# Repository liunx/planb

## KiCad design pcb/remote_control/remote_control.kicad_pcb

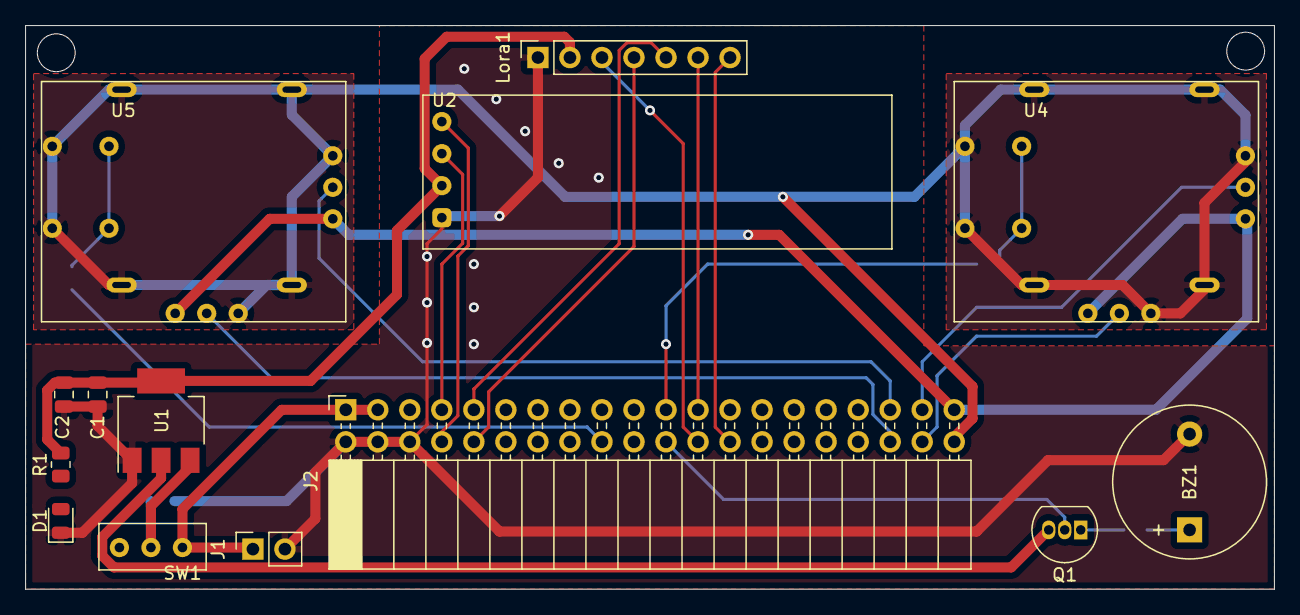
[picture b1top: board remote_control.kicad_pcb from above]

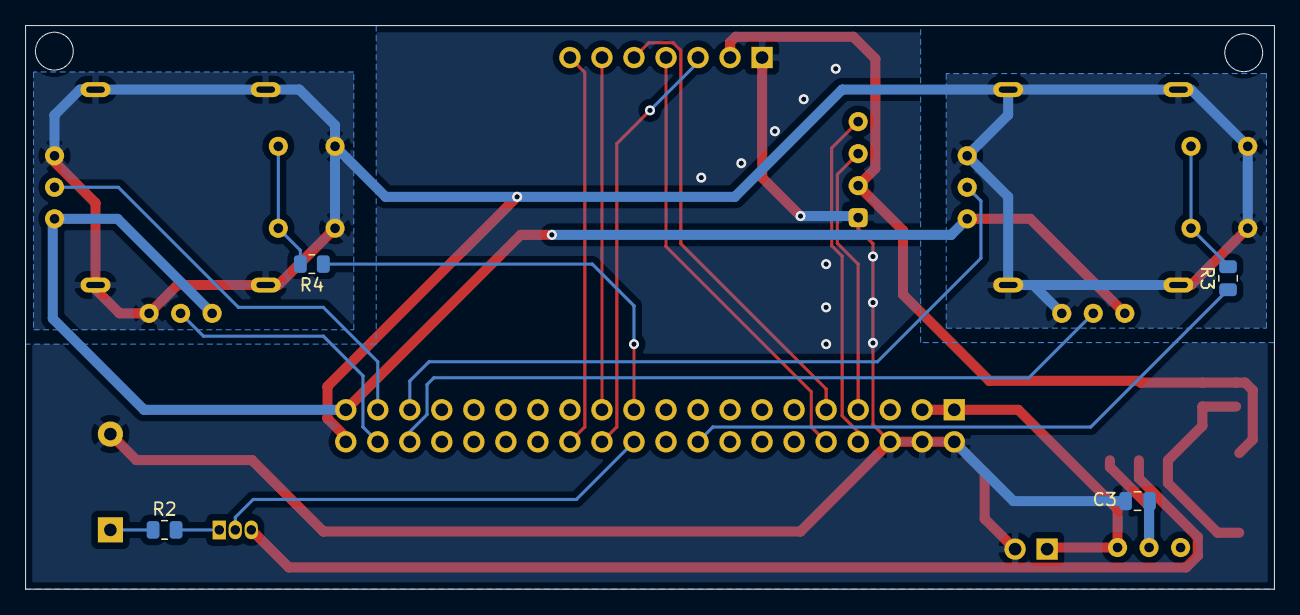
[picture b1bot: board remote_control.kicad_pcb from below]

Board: 2 copper layers, 99.1 x 44.7 mm, 18 parts (4 on the bottom side), 25 nets.

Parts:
BZ1: Buzzer; Buzzer_12x9.5RM7.6
C1, C3: 10uF; C_0805_2012Metric
C2: 100nF; C_0805_2012Metric
D1: LED; LED_0805_2012Metric
J1: Conn_01x02; PinSocket_1x02_P2.54mm_Vertical
J2: Conn_02x20_Odd_Even; PinSocket_2x20_P2.54mm_Horizontal
Lora1: Conn_01x07; PinSocket_1x07_P2.54mm_Vertical
Q1: S8050; TO-92_Inline
R1, R2, R3, R4: 510R; R_0805_2012Metric
SW1: SW_Push; SS12D00
U1: AMS1117-5.0; SOT-223-3_TabPin2
U2: OLED0.91''; OLED_0.91
U4, U5: Rocker

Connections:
+3.3VA: J2.39, U4.5, U5.5
+5V: C1.1, C2.1, Lora1.2, Q1.3, R1.2, U1.2, U2.2
/PA0: J2.37, U4.1
/PA1: J2.38, U4.2
/PA2: J2.35, U5.1
/PA3: J2.36, U5.2
/PA8: J2.22, Q1.2
/PA12: J2.18, R3.1
/PB6: J2.9, Lora1.5
/PB7: J2.10, Lora1.4
/PB8: J2.7, U2.3
/PB9: J2.8, U2.4
/PB12: J2.26, Lora1.7
/PB13: J2.23, Lora1.6
/PB14: J2.24, Lora1.3
/PB15: J2.21, R4.1
GNDA: J2.40, U4.4, U5.4
GNDD: BZ1.2, C1.2, C2.2, C3.2, D1.1, J1.2, J2.2, J2.4, J2.6, Lora1.1, U1.1, U2.1
unnamed: BZ1.1, R2.1
unnamed: C3.1, SW1.2, U1.3
unnamed: D1.2, R1.1
unnamed: Q1.1, R2.2
unnamed: R3.2, U5.3
unnamed: R4.2, U4.3
VCC: J1.1, J2.1, J2.3, SW1.1

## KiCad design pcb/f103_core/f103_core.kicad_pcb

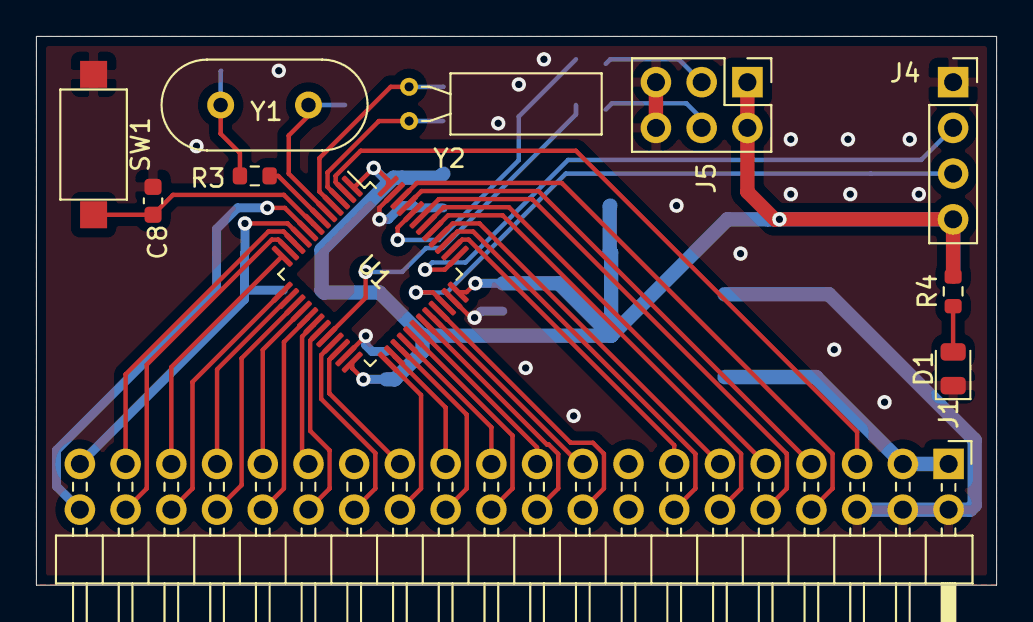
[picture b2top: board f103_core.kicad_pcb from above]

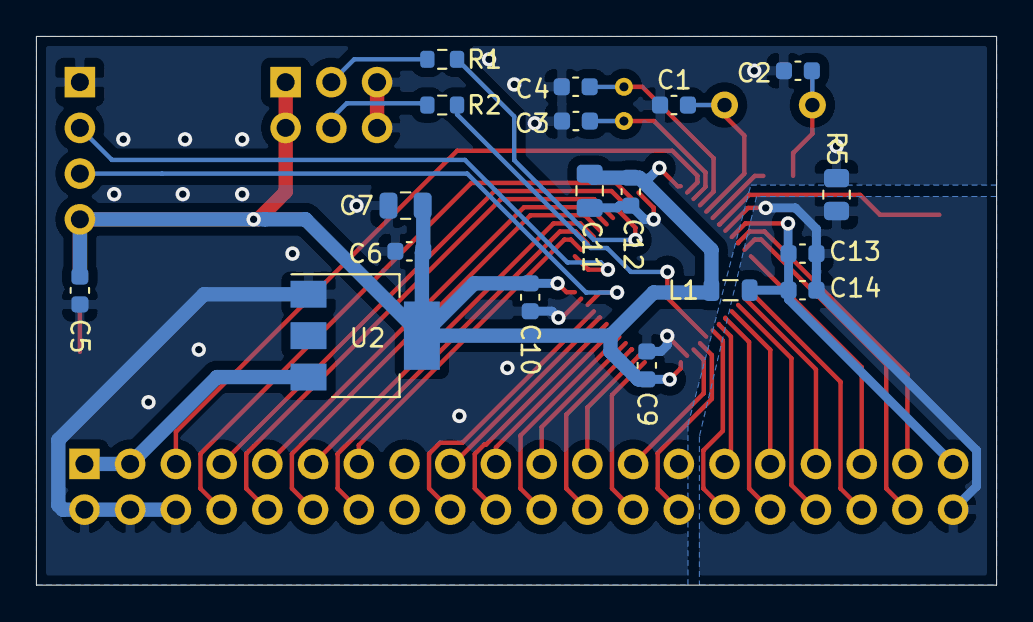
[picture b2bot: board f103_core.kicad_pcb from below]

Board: 2 copper layers, 53.3 x 30.5 mm, 29 parts (18 on the bottom side), 48 nets.

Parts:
C1, C2: 20pF; C_0603_1608Metric
C3, C4, C8: 10pF; C_0603_1608Metric
C5, C7, C9, C10, C12: 100nF; C_0603_1608Metric
C6: 10uF; C_0805_2012Metric
C11: 4.7uF; C_0805_2012Metric
C13: 1uF; C_0603_1608Metric
C14: 10nF; C_0603_1608Metric
D1: LED; LED_0805_2012Metric
J1: Conn_02x20_Odd_Even; PinHeader_2x20_P2.54mm_Horizontal
J4: Conn_01x04; PinSocket_1x04_P2.54mm_Vertical
J5: Conn_02x03_Odd_Even; PinHeader_2x03_P2.54mm_Vertical
L1: 10uH; L_0805_2012Metric
R1, R2: 10K; R_0603_1608Metric
R3: 390; R_0603_1608Metric
R4: 510R; R_0603_1608Metric
R5: 0R; R_0805_2012Metric
SW1: SW_Push; SW_SPST_CK_RS282G05A3
U1: STM32F103C6Tx; LQFP-48_7x7mm_P0.5mm
U2: AMS1117-3.3; SOT-223-3_TabPin2
Y1: 8M; Crystal_HC49-4H_Vertical
Y2: 32.768; Crystal_C38-LF_D3.0mm_L8.0mm_Horizontal

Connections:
+3.3VA: C13.1, C14.1, J1.39, L1.2, U1.9
+3V3: C5.1, C6.1, C7.1, C9.1, C10.1, C11.1, C12.1, J4.4, J5.1, J5.2, L1.1, R4.2, U1.1, U1.24, U1.36, U1.48, U2.2
/BOOT0: R1.2, U1.44
/BOOT1: R2.1, U1.20
/PA0: J1.37, U1.10
/PA1: J1.38, U1.11
/PA2: J1.35, U1.12
/PA3: J1.36, U1.13
/PA4: J1.33, U1.14
/PA5: J1.34, U1.15
/PA6: J1.31, U1.16
/PA7: J1.32, U1.17
/PA8: J1.22, U1.29
/PA9: J1.19, U1.30
/PA10: J1.20, U1.31
/PA11: J1.17, U1.32
/PA12: J1.18, U1.33
/PA15: J1.13, U1.38
/PB0: J1.29, U1.18
/PB1: J1.30, U1.19
/PB3: J1.14, U1.39
/PB4: J1.11, U1.40
/PB5: J1.12, U1.41
/PB6: J1.9, U1.42
/PB7: J1.10, U1.43
/PB8: J1.7, U1.45
/PB9: J1.8, U1.46
/PB10: J1.28, U1.21
/PB11: J1.25, U1.22
/PB12: J1.26, U1.25
/PB13: J1.23, U1.26
/PB14: J1.24, U1.27
/PB15: J1.21, U1.28
/PC13: J1.5, U1.2
/RCC_OSC32_IN: C3.2, U1.3, Y2.1
/RCC_OSC32_OUT: C4.2, U1.4, Y2.2
/RCC_OSC_IN: C1.2, U1.5, Y1.1
/RCC_OSC_OUT: R3.2, U1.6
/SYS_JTCK-SWCL: J4.2, U1.37
/SYS_JTMS-SWDIO: J4.3, U1.34
GND: C1.1, C2.1, C3.1, C4.1, C5.2, C6.2, C7.2, C8.2, C9.2, C10.2, C11.2, C12.2, D1.1, J1.2, J1.4, J1.6, J4.1, J5.5, J5.6, R5.1, SW1.1, U1.23, U1.35, U1.47, U2.1
GNDA: C13.2, C14.2, J1.40, R5.2, U1.8
unnamed: C2.2, R3.1, Y1.2
unnamed: D1.2, R4.1
unnamed: J5.3, R1.1
unnamed: J5.4, R2.2
RESET: C8.1, SW1.2, U1.7
VCC: J1.1, J1.3, U2.3

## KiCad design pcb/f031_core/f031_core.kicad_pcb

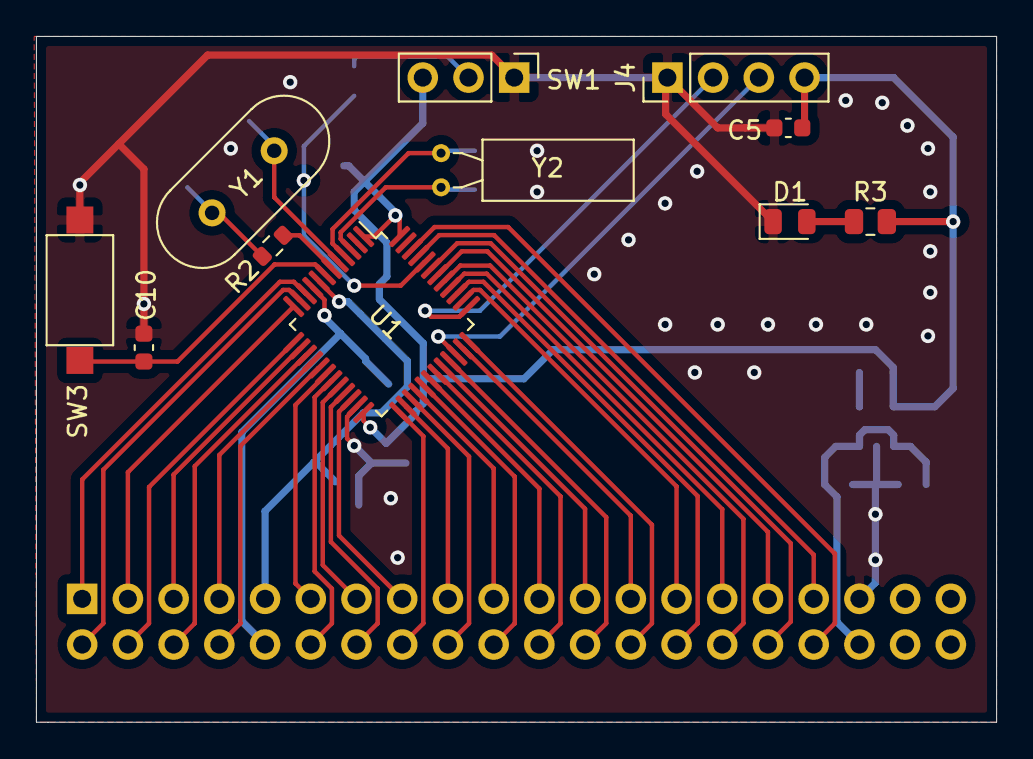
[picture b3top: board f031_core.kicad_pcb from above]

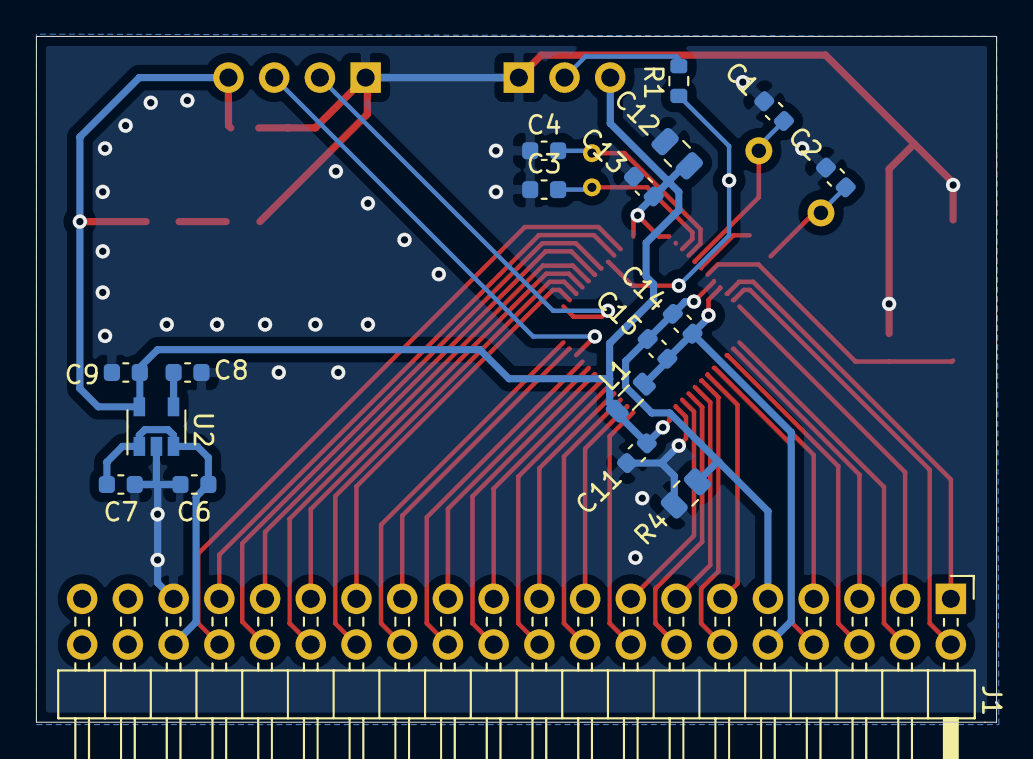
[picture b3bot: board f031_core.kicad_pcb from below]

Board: 2 copper layers, 53.3 x 38.1 mm, 29 parts (18 on the bottom side), 49 nets.

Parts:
C1, C2: 20pF; C_0603_1608Metric
C3, C4: 10pF; C_0603_1608Metric
C5, C7, C10, C11, C13: 100nF; C_0603_1608Metric
C6: 10uF; C_0603_1608Metric
C8: 470pF; C_0603_1608Metric
C9: 2.2uF; C_0603_1608Metric
C12: 4.7uF; C_0805_2012Metric
C14: 1uF; C_0603_1608Metric
C15: 10nF; C_0603_1608Metric
D1: LED; LED_0805_2012Metric
J1: Conn_02x20_Odd_Even; PinHeader_2x20_P2.54mm_Horizontal
J4: Conn_01x04; PinHeader_1x04_P2.54mm_Vertical
L1: 10uH; L_0805_2012Metric
R1: 10K; R_0603_1608Metric
R2: 390; R_0603_1608Metric
R3: 510R; R_0805_2012Metric
R4: 0R; R_0805_2012Metric
SW1: SW_DPDT_x2; PinHeader_1x03_P2.54mm_Vertical
SW3: SW_Push; SW_SPST_CK_RS282G05A3
U1: STM32F031C6Tx; LQFP-48_7x7mm_P0.5mm
U2: MIC5219-3.3YM5; SOT-23-5
Y1: 8M; Crystal_HC49-4H_Vertical
Y2: 32.768; Crystal_C38-LF_D3.0mm_L8.0mm_Horizontal

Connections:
+3.3VA: C14.1, C15.1, J1.10, L1.1, U1.9
+3V3: C5.1, C9.1, C11.1, C12.1, C13.1, J4.4, L1.2, R3.2, SW1.3, U1.1, U1.24, U1.48, U2.5
/BOOT0: R1.2, U1.44
/PA0: J1.1, U1.10
/PA1: J1.2, U1.11
/PA2: J1.3, U1.12
/PA3: J1.4, U1.13
/PA4: J1.5, U1.14
/PA5: J1.6, U1.15
/PA6: J1.7, U1.16
/PA7: J1.8, U1.17
/PA8: J1.20, U1.29
/PA9: J1.21, U1.30
/PA10: J1.22, U1.31
/PA11: J1.23, U1.32
/PA12: J1.24, U1.33
/PA15: J1.27, U1.38
/PB0: J1.11, U1.18
/PB1: J1.12, U1.19
/PB2: J1.13, U1.20
/PB3: J1.28, U1.39
/PB4: J1.29, U1.40
/PB5: J1.30, U1.41
/PB6: J1.31, U1.42
/PB7: J1.32, U1.43
/PB8: J1.33, U1.45
/PB9: J1.34, U1.46
/PB10: J1.14, U1.21
/PB11: J1.15, U1.22
/PB12: J1.16, U1.25
/PB13: J1.17, U1.26
/PB14: J1.18, U1.27
/PB15: J1.19, U1.28
/PF6: J1.25, U1.35
/PF7: J1.26, U1.36
/RCC_OSC32_IN: C3.2, U1.3, Y2.1
/RCC_OSC32_OUT: C4.2, U1.4, Y2.2
/RCC_OSC_IN: C1.2, U1.5, Y1.1
/RCC_OSC_OUT: R2.2, U1.6
/SYS_SWCL: J4.2, U1.37
/SYS_SWDIO: J4.3, U1.34
GND: C1.1, C2.1, C3.1, C4.1, C5.2, C6.2, C7.2, C8.2, C9.2, C10.2, C11.2, C12.2, C13.2, D1.1, J1.35, J4.1, R4.1, SW1.1, SW3.1, U1.23, U1.47, U2.2
GNDA: C14.2, C15.2, J1.9, R4.2, U1.8
unnamed: C2.2, R2.1, Y1.2
unnamed: C8.1, U2.4
unnamed: D1.2, R3.1
unnamed: R1.1, SW1.2
RESET: C10.1, SW3.2, U1.7
VCC: C6.1, C7.1, J1.36, U2.1, U2.3

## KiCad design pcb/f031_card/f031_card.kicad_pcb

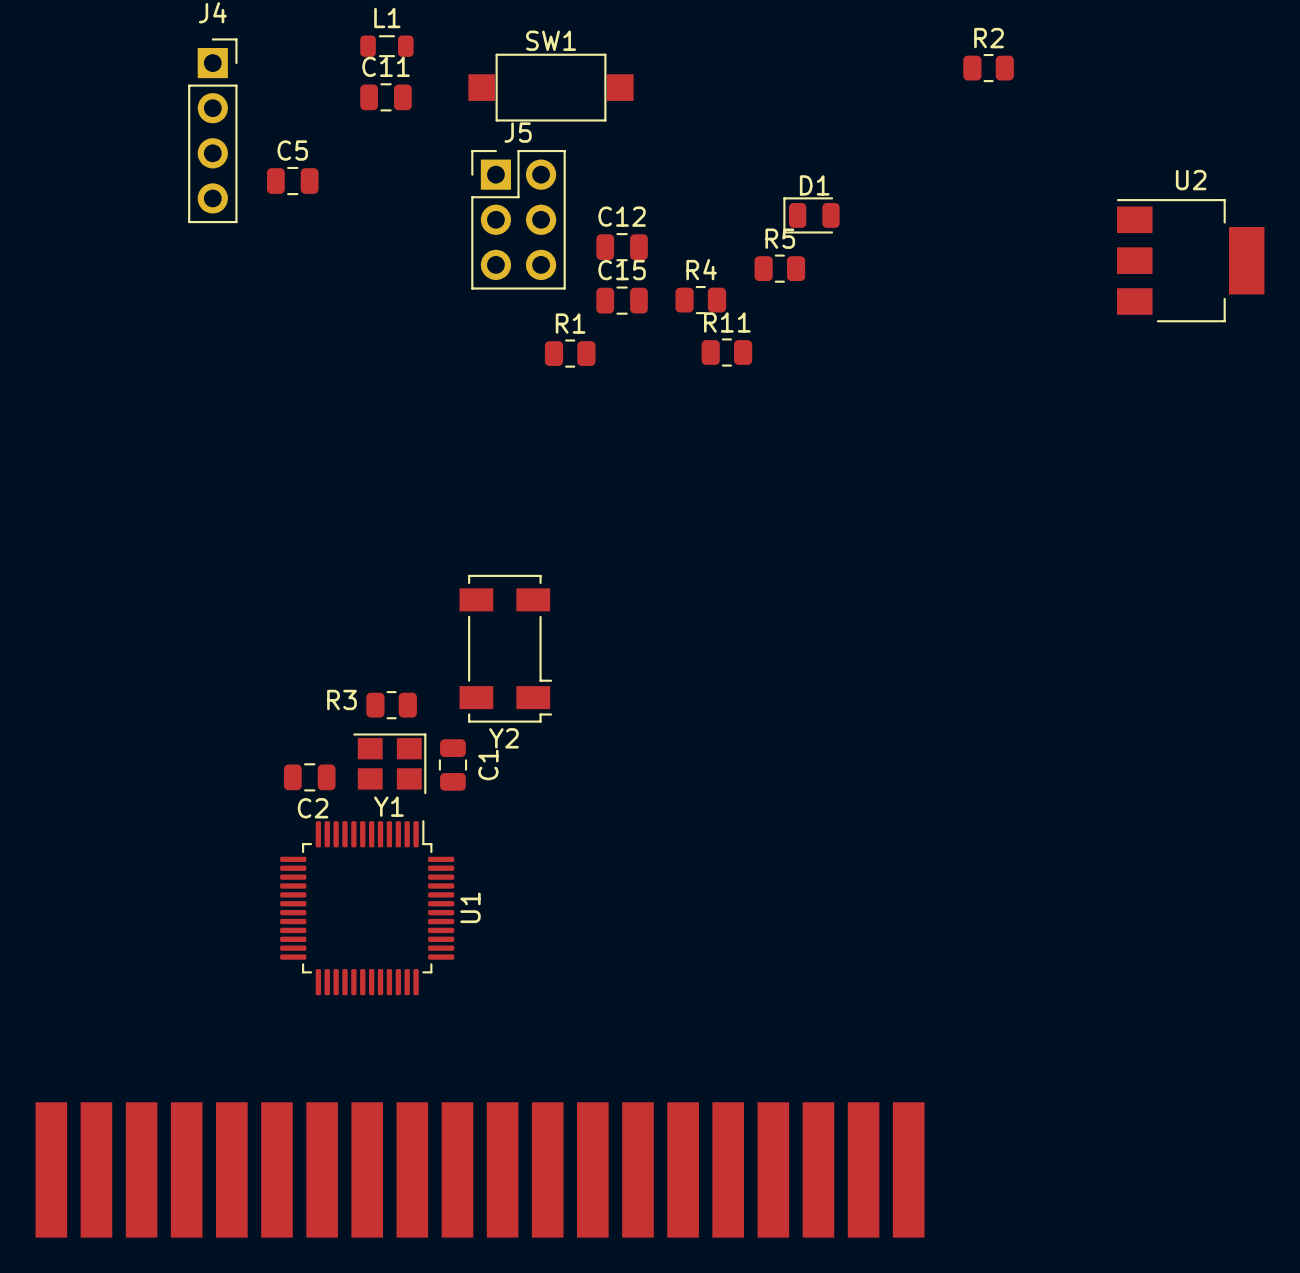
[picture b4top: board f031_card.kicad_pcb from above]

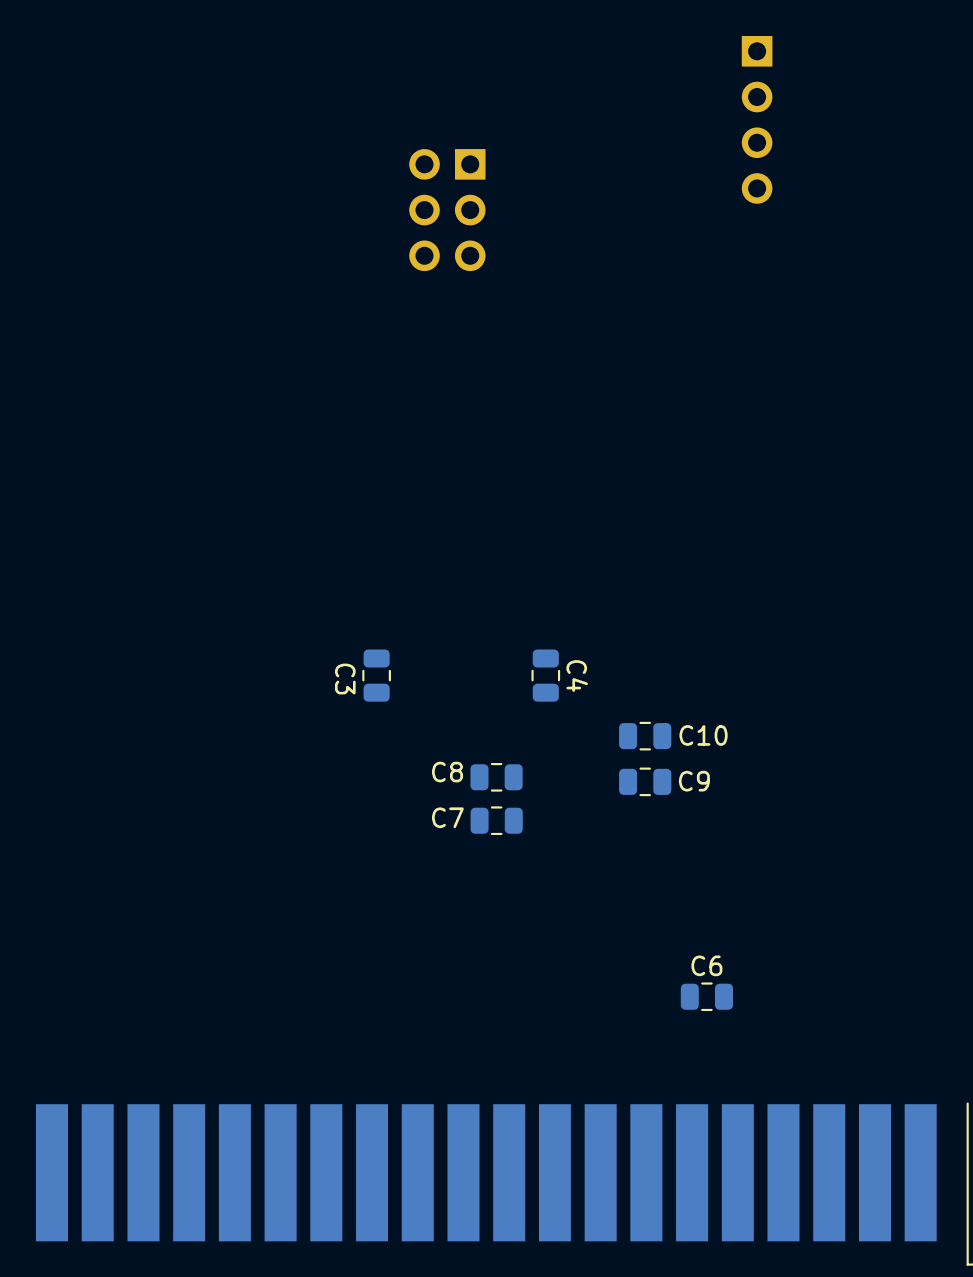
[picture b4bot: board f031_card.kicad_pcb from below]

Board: 2 copper layers, 29 parts (8 on the bottom side), 48 nets, no tracks yet.

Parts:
C1, C2, C3, C4: 20pF; C_0805_2012Metric
C5, C6, C8, C12: 0.1uF; C_0805_2012Metric
C7: 4.7uF; C_0805_2012Metric
C9: 1uF; C_0805_2012Metric
C10: 10nF; C_0805_2012Metric
C11: 10uF; C_0805_2012Metric
C15: 10pF; C_0805_2012Metric
D1: LED; LED_0805_2012Metric
J1: Conn_02x20_Top_Bottom; BUS_2x20_2.54mm_Vertical_SMD
J4: Conn_01x04; PinSocket_1x04_P2.54mm_Vertical
J5: Conn_02x03_Odd_Even; PinHeader_2x03_P2.54mm_Vertical
L1: 10uH; L_0805_2012Metric
R1, R2: 100K; R_0805_2012Metric
R3: 10M; R_0805_2012Metric
R4: 0R; R_0805_2012Metric
R5, R11: 510R; R_0805_2012Metric
SW1: SW_Push; SW_SPST_CK_RS282G05A3
U1: STM32F031C6Tx; LQFP-48_7x7mm_P0.5mm
U2: AMS1117-3.3; SOT-223-3_TabPin2
Y1: 8M; Crystal_SMD_3225-4Pin_3.2x2.5mm
Y2: 32768HZ; Crystal_SMD_Abracon_ABS25-4Pin_8.0x3.8mm

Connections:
+3.3VA: C9.1, C10.1, J1.1, J1.21, L1.2, U1.9
+3V3: C5.1, C6.1, C7.1, C8.1, C11.1, C12.1, J4.4, J5.1, J5.2, L1.1, R5.2, R11.2, U1.24, U1.48, U2.2
/BOOT0: R1.2, U1.44
/BOOT1: R2.1, U1.20
/PA0: J1.3, U1.10
/PA1: J1.4, U1.11
/PA2: J1.5, U1.12
/PA3: J1.6, U1.13
/PA4: J1.7, U1.14
/PA5: J1.8, U1.15
/PA6: J1.9, U1.16
/PA7: J1.10, U1.17
/PA8: J1.22, U1.29
/PA9: J1.23, U1.30
/PA10: J1.24, U1.31
/PA11: J1.25, U1.32
/PA12: J1.26, U1.33
/PA13: J1.27, J4.3, U1.34
/PA14: J1.30, J4.2, U1.37
/PA15: J1.31, U1.38
/PB0: J1.11, U1.18
/PB1: J1.12, U1.19
/PB3: J1.32, U1.39
/PB4: J1.33, U1.40
/PB5: J1.34, U1.41
/PB6: J1.35, U1.42
/PB7: J1.36, U1.43
/PB8: J1.37, U1.45
/PB9: J1.38, U1.46
/PB10: J1.13, U1.21
/PB11: J1.14, U1.22
/PB12: J1.15, U1.25
/PB13: J1.16, U1.26
/PB14: J1.17, U1.27
/PB15: J1.18, U1.28
/PF6: J1.28, U1.35
/PF7: J1.29, U1.36
/RCC_OSC32_IN: C3.2, U1.3, Y2.1
/RCC_OSC32_OUT: C4.2, U1.4, Y2.4
/RCC_OSC_IN: C1.2, R3.2, U1.5, Y1.1
/RCC_OSC_OUT: C2.2, R3.1, U1.6, Y1.3
GND: C1.1, C2.1, C3.1, C4.1, C5.2, C6.2, C7.2, C8.2, C9.2, C10.2, C11.2, C12.2, C15.2, D1.1, J1.20, J1.40, J4.1, J5.5, J5.6, R4.1, SW1.1, U1.23, U1.47, U2.1, Y1.2, Y1.4
GNDA: J1.2, R4.2, U1.8
unnamed: D1.2, R5.1
unnamed: J5.3, R1.1
unnamed: J5.4, R2.2
RESET: C15.1, R11.1, SW1.2, U1.7
VCC: J1.19, J1.39, U2.3

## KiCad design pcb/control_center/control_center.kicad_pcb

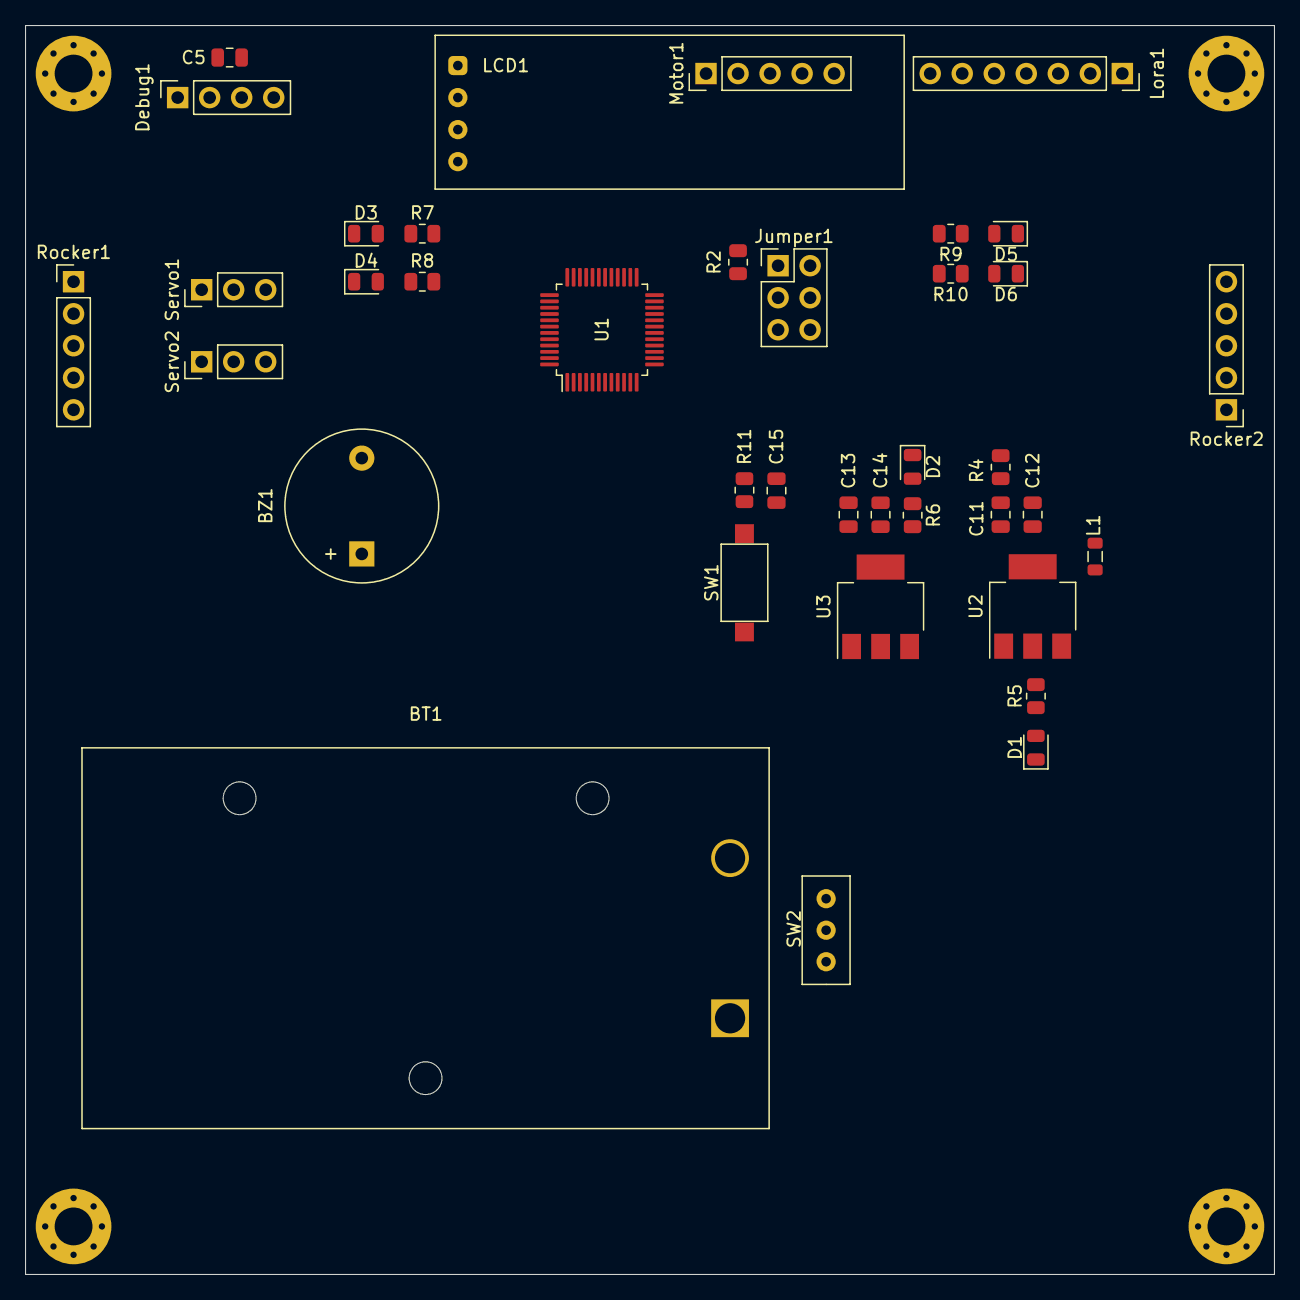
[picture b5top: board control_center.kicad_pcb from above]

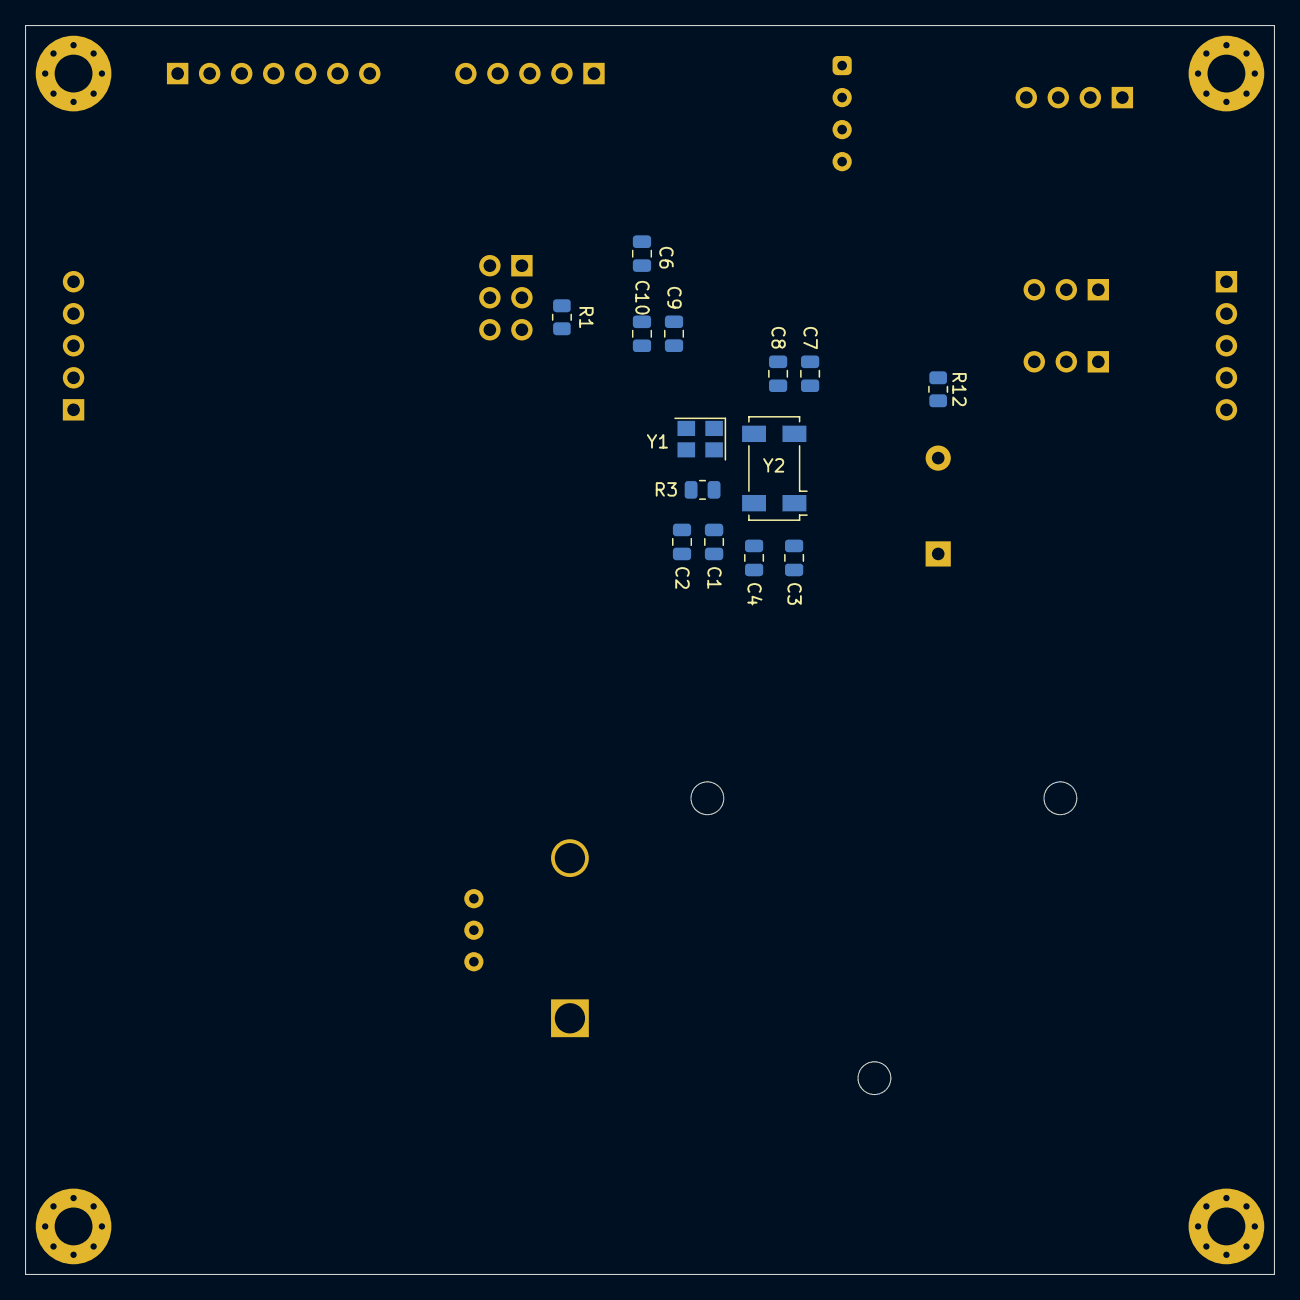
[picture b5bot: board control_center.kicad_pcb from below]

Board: 2 copper layers, 99.1 x 99.1 mm, 56 parts (14 on the bottom side), 49 nets, no tracks yet.

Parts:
BT1: Battery; BatteryHolder_Eagle_12BH611-GR
BZ1: Buzzer; Buzzer_12x9.5RM7.6
C1, C2, C3, C4: 20pF; C_0805_2012Metric
C5, C6, C8, C12, C14: 0.1uF; C_0805_2012Metric
C7: 4.7uF; C_0805_2012Metric
C9: 1uF; C_0805_2012Metric
C10: 10nF; C_0805_2012Metric
C11, C13: 10uF; C_0805_2012Metric
C15: 10pF; C_0805_2012Metric
D1, D2, D3, D4, D5, D6: LED; LED_0805_2012Metric
Debug1: Conn_01x04; PinSocket_1x04_P2.54mm_Vertical
Jumper1: Conn_02x03_Odd_Even; PinHeader_2x03_P2.54mm_Vertical
L1: 10uH; L_0805_2012Metric
LCD1: Conn_01x04; OLED0.91Inch
Lora1: Conn_01x07; PinSocket_1x07_P2.54mm_Vertical
Motor1: Conn_01x05; PinHeader_1x05_P2.54mm_Vertical
Pad1, Pad2, Pad3, Pad4: MountingHole_3mm_Pad_Via
R1, R2: 100K; R_0805_2012Metric
R3: 10M; R_0805_2012Metric
R4: 0R; R_0805_2012Metric
R5, R6, R7, R8, R9, R10, R11, R12: 510R; R_0805_2012Metric
Rocker1, Rocker2: Conn_01x05; PinHeader_1x05_P2.54mm_Vertical
SW1: SW_Push; SW_SPST_CK_RS282G05A3
SW2: SW_Push; SS12D00
Servo1, Servo2: Conn_01x03; PinHeader_1x03_P2.54mm_Vertical
U1: STM32F031C6Tx; LQFP-48_7x7mm_P0.5mm
U2: AMS1117-3.3; SOT-223-3_TabPin2
U3: AMS1117-5.0; SOT-223-3_TabPin2
Y1: 8M; Crystal_SMD_3225-4Pin_3.2x2.5mm
Y2: 32768HZ; Crystal_SMD_Abracon_ABS25-4Pin_8.0x3.8mm

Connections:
+3.3VA: C9.1, C10.1, L1.1, Rocker1.2, Rocker2.2, U1.9
+9V: SW2.2, U2.3, U3.3
/AUX: Lora1.3, U1.27
/BOOT0: R1.2, U1.44
/BOOT1: R2.1, U1.20
/I2C1_SCL: LCD1.3, U1.35
/I2C1_SDA: LCD1.4, U1.36
/MD0: Lora1.7, U1.25
/MD1: Lora1.6, U1.26
/RCC_OSC32_IN: C3.2, U1.3, Y2.1
/RCC_OSC32_OUT: C4.2, U1.4, Y2.4
/RCC_OSC_IN: C1.2, R3.2, U1.5, Y1.1
/RCC_OSC_OUT: C2.2, R3.1, U1.6, Y1.3
/RX1: Rocker1.3, U1.10
/RX2: Rocker2.3, U1.13
/RY1: Rocker1.4, U1.11
/RY2: Rocker2.4, U1.14
/SW1: Rocker1.5, U1.12
/SW2: Rocker2.5, U1.15
/SYS_SWCL: Debug1.2, U1.37
/SYS_SWDIO: Debug1.3, U1.34
/TIM1_CH1: Motor1.5, U1.29
/TIM1_CH2: Motor1.4, U1.30
/TIM1_CH3: Motor1.3, U1.31
/TIM1_CH4: Motor1.2, U1.32
/TIM2_CH1: R7.2, U1.38
/TIM2_CH2: R8.2, U1.39
/TIM2_CH3: R9.2, U1.21
/TIM2_CH4: R10.2, U1.22
/TIM3_CH1: Servo1.3, U1.40
/TIM3_CH2: Servo2.3, U1.41
/TIM16_CH1: R12.2, U1.45
/USART1_RX: Lora1.4, U1.43
/USART1_TX: Lora1.5, U1.42
/V3.3: C5.1, C6.1, C7.1, C8.1, C11.1, C12.1, Debug1.4, Jumper1.1, Jumper1.2, L1.2, LCD1.2, R5.2, R11.2, U1.24, U1.48, U2.2
/V5.0: C13.1, C14.1, Lora1.2, R6.2, Servo1.2, Servo2.2, U3.2
GND: BT1.2, BZ1.2, C1.1, C2.1, C3.1, C4.1, C5.2, C6.2, C7.2, C8.2, C9.2, C10.2, C11.2, C12.2, C13.2, C14.2, C15.2, D1.1, D2.1, D3.1, D4.1, D5.1, D6.1, Debug1.1, Jumper1.5, Jumper1.6, LCD1.1, Lora1.1, Motor1.1, R4.1, SW1.1, Servo1.1, Servo2.1, U1.23, U1.47, U2.1, U3.1, Y1.2, Y1.4
GNDA: R4.2, Rocker1.1, Rocker2.1, U1.8
unnamed: BT1.1, SW2.1
unnamed: BZ1.1, R12.1
unnamed: D1.2, R5.1
unnamed: D2.2, R6.1
unnamed: D3.2, R7.1
unnamed: D4.2, R8.1
unnamed: D5.2, R9.1
unnamed: D6.2, R10.1
unnamed: Jumper1.3, R1.1
unnamed: Jumper1.4, R2.2
RESET: C15.1, R11.1, SW1.2, U1.7
